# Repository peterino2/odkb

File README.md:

# ODKB - Collection repository for the stm32 based keyboard project

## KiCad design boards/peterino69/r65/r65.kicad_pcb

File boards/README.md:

# Boards

This is a submodul of the odkb\_top repositoy.

These files were intially created in kicad 4 but will be migrated to kicad five

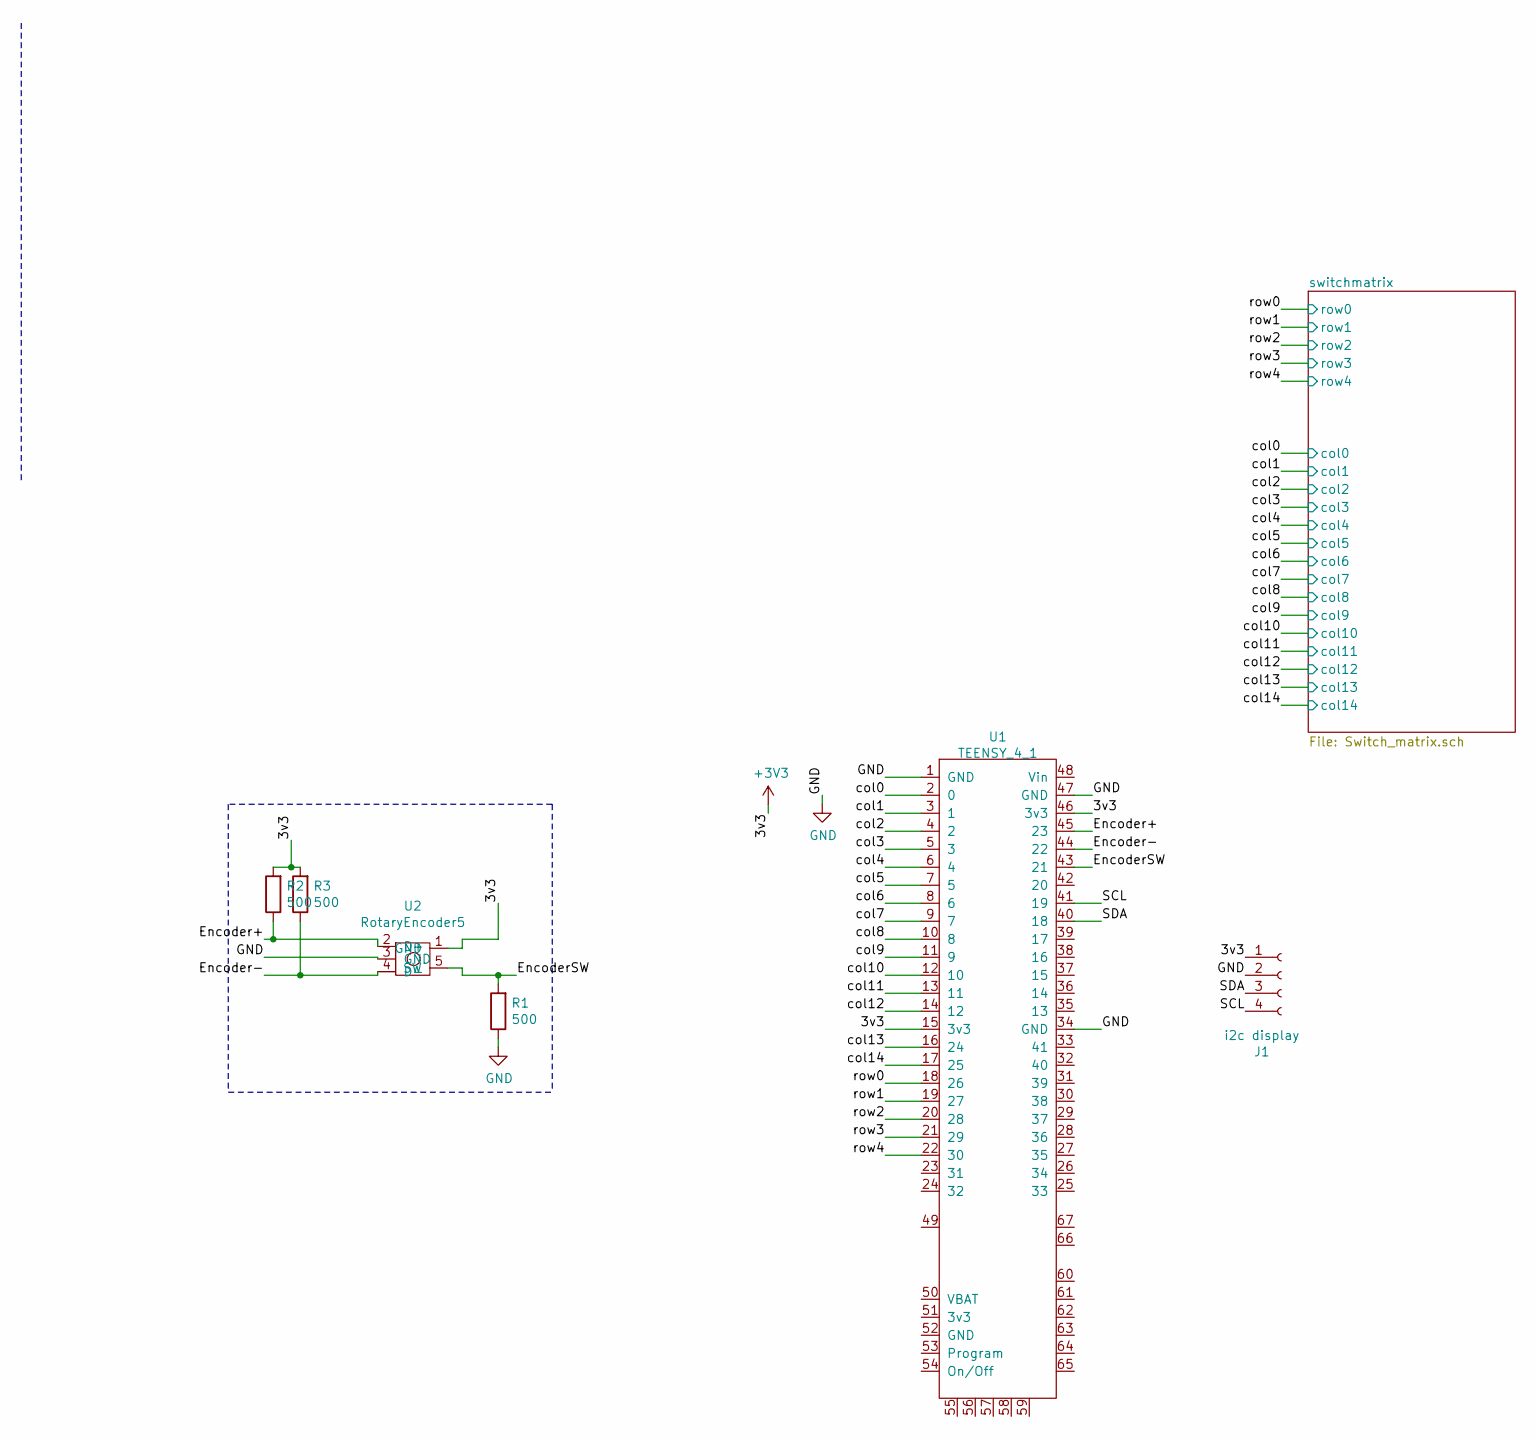
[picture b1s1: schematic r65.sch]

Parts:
J1: i2c display; LCD_DISPLAY
R1, R2, R3: 500; R_Axial_DIN0207_L6.3mm_D2.5mm_P15.24mm_Horizontal
U1: TEENSY_4_1; Teensy41_no_inners
U2: RotaryEncoder5; SF-ROTARY-ENCODER

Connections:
+3V3: J1.1, R2.2, R3.2, U1.15 (3v3), U1.46 (3v3), U2.1 (GND)
/Encoder+: R2.1, U1.45 (23), U2.2 (D+)
/Encoder-: R3.1, U1.44 (22), U2.4 (D-)
/EncoderSW: R1.2, U1.43 (21), U2.5 (SW)
/SCL: J1.4, U1.41 (19)
/SDA: J1.3, U1.40 (18)
/col0: U1.2 (0); also elsewhere on the board
/col1: U1.3 (1); also elsewhere on the board
/col2: U1.4 (2); also elsewhere on the board
/col3: U1.5 (3); also elsewhere on the board
/col4: U1.6 (4); also elsewhere on the board
/col5: U1.7 (5); also elsewhere on the board
/col6: U1.8 (6); also elsewhere on the board
/col7: U1.9 (7); also elsewhere on the board
/col8: U1.10 (8); also elsewhere on the board
/col9: U1.11 (9); also elsewhere on the board
/col10: U1.12 (10); also elsewhere on the board
/col11: U1.13 (11); also elsewhere on the board
/col12: U1.14 (12); also elsewhere on the board
/col13: U1.16 (24); also elsewhere on the board
/col14: U1.17 (25); also elsewhere on the board
/row0: U1.18 (26); also elsewhere on the board
/row1: U1.19 (27); also elsewhere on the board
/row2: U1.20 (28); also elsewhere on the board
/row3: U1.21 (29); also elsewhere on the board
/row4: U1.22 (30); also elsewhere on the board
GND: J1.2, R1.1, U1.1 (GND), U1.34 (GND), U1.47 (GND), U2.3 (GND)

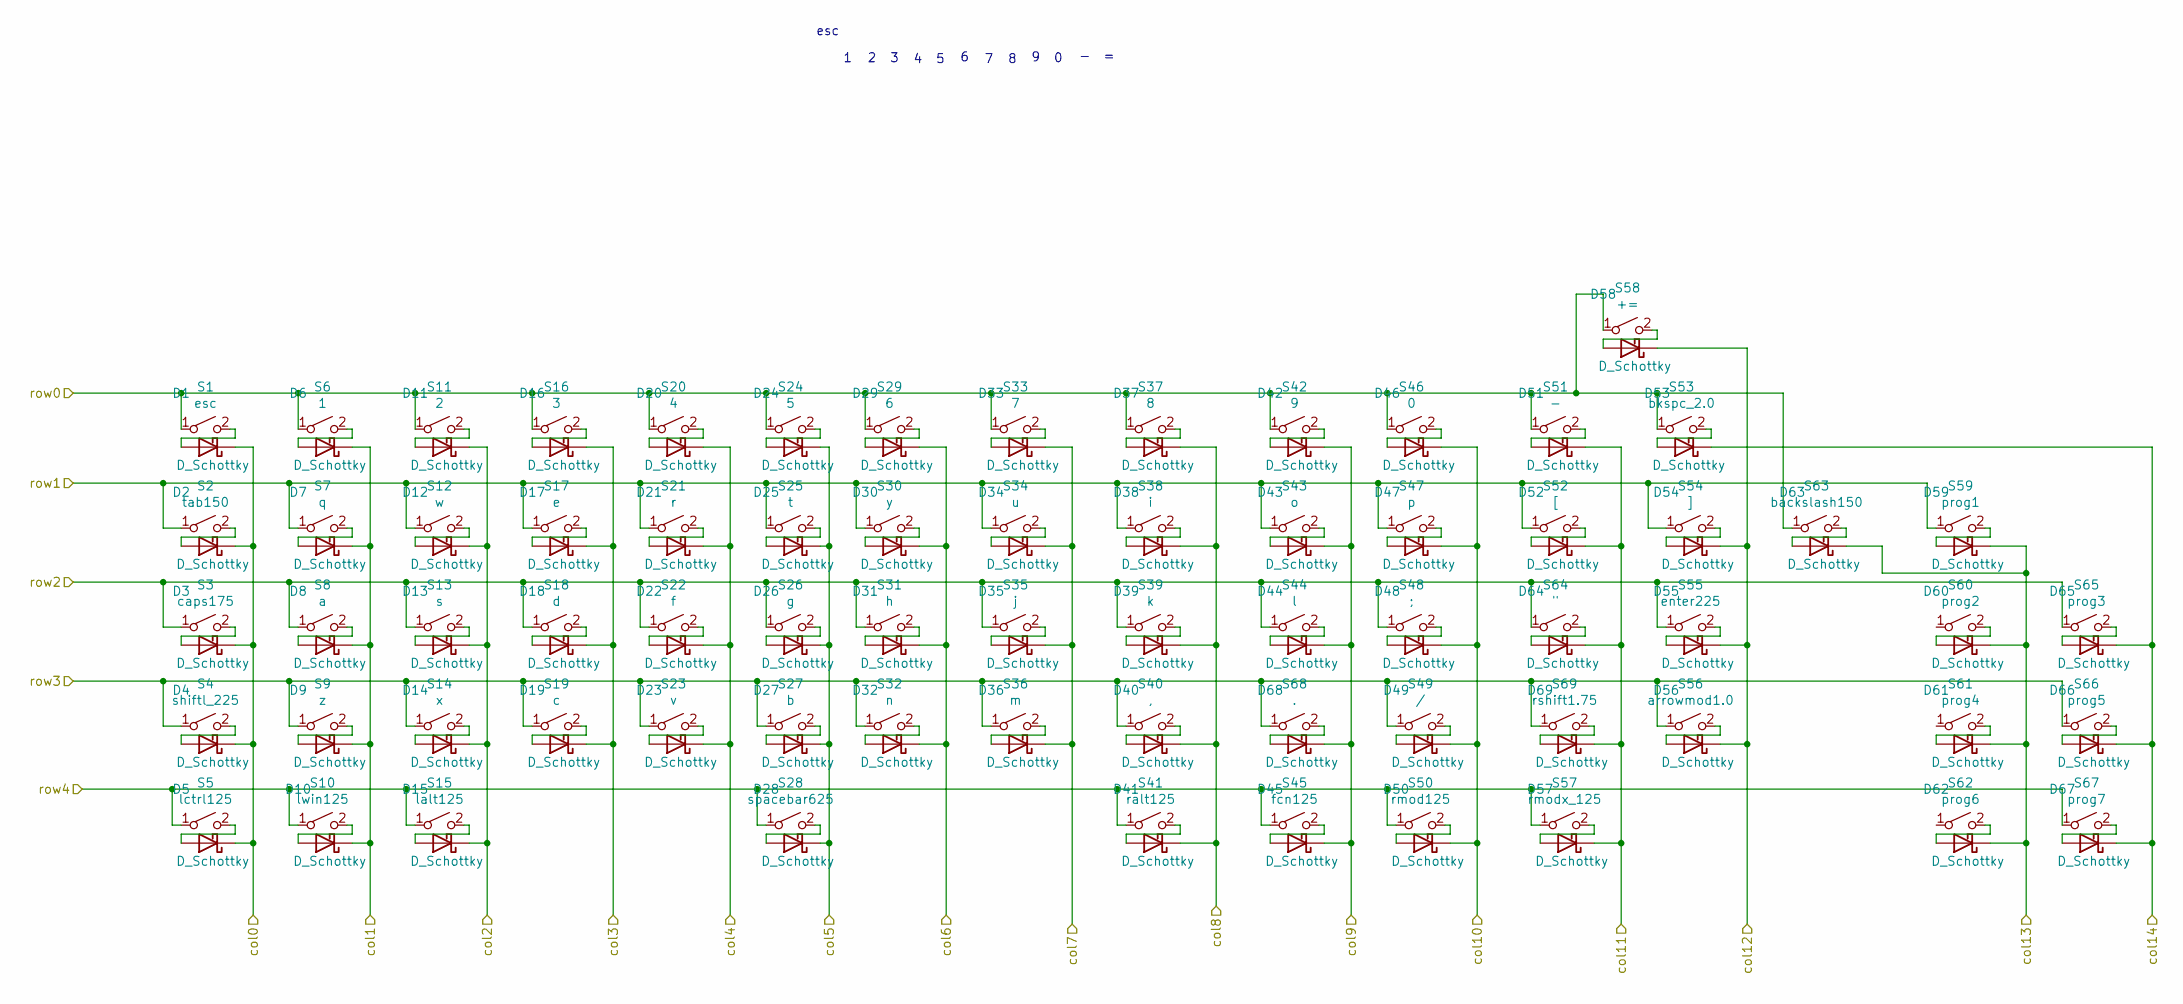
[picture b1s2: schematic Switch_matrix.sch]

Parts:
D1, D2, D3, D4, D5, D6, D7, D8, D9, D10, D11, D12, D13, D14, D15, D16, D17, D18, D19, D20, D21, D22, D23, D24, D25, D26, D27, D28, D29, D30, D31, D32, D33, D34, D35, D36, D37, D38, D39, D40, D41, D42, D43, D44, D45, D46, D47, D48, D49, D50, D51, D52, D53, D54, D55, D56, D57, D58, D59, D60, D61, D62, D63, D64, D65, D66, D67, D68, D69: D_Schottky; D_DO-41_SOD81_P10.16mm_Horizontal
S1: esc; SW_Cherry_MX_1.00u_Plate
S2: tab150; SW_Cherry_MX_1.50u_PCB
S3: caps175; SW_Cherry_MX_1.75u_PCB
S4: shiftl_225; SW_Cherry_MX_2.25u_PCB
S5: lctrl125; SW_Cherry_MX_1.25u_PCB
S6: 1; SW_Cherry_MX_1.00u_Plate
S7: q; SW_Cherry_MX_1.00u_Plate
S8: a; SW_Cherry_MX_1.00u_Plate
S9: z; SW_Cherry_MX_1.00u_Plate
S10: lwin125; SW_Cherry_MX_1.25u_PCB
S11: 2; SW_Cherry_MX_1.00u_Plate
S12: w; SW_Cherry_MX_1.00u_Plate
S13: s; SW_Cherry_MX_1.00u_Plate
S14: x; SW_Cherry_MX_1.00u_Plate
S15: lalt125; SW_Cherry_MX_1.25u_PCB
S16: 3; SW_Cherry_MX_1.00u_Plate
S17: e; SW_Cherry_MX_1.00u_Plate
S18: d; SW_Cherry_MX_1.00u_Plate
S19: c; SW_Cherry_MX_1.00u_Plate
S20: 4; SW_Cherry_MX_1.00u_Plate
S21: r; SW_Cherry_MX_1.00u_Plate
S22: f; SW_Cherry_MX_1.00u_Plate
S23: v; SW_Cherry_MX_1.00u_Plate
S24: 5; SW_Cherry_MX_1.00u_Plate
S25: t; SW_Cherry_MX_1.00u_Plate
S26: g; SW_Cherry_MX_1.00u_Plate
S27: b; SW_Cherry_MX_1.00u_Plate
S28: spacebar625; SW_Cherry_MX_6.25u_PCB
S29: 6; SW_Cherry_MX_1.00u_Plate
S30: y; SW_Cherry_MX_1.00u_Plate
S31: h; SW_Cherry_MX_1.00u_Plate
S32: n; SW_Cherry_MX_1.00u_Plate
S33: 7; SW_Cherry_MX_1.00u_Plate
S34: u; SW_Cherry_MX_1.00u_Plate
S35: j; SW_Cherry_MX_1.00u_Plate
S36: m; SW_Cherry_MX_1.00u_Plate
S37: 8; SW_Cherry_MX_1.00u_Plate
S38: i; SW_Cherry_MX_1.00u_Plate
S39: k; SW_Cherry_MX_1.00u_Plate
S40: ,; SW_Cherry_MX_1.00u_Plate
S41: ralt125; SW_Cherry_MX_1.25u_PCB
S42: 9; SW_Cherry_MX_1.00u_Plate
S43: o; SW_Cherry_MX_1.00u_Plate
S44: l; SW_Cherry_MX_1.00u_Plate
S45: fcn125; SW_Cherry_MX_1.25u_PCB
S46: 0; SW_Cherry_MX_1.00u_Plate
S47: p; SW_Cherry_MX_1.00u_Plate
S48: ;; SW_Cherry_MX_1.00u_Plate
S49: /; SW_Cherry_MX_1.00u_Plate
S50: rmod125; SW_Cherry_MX_1.25u_PCB
S51: -; SW_Cherry_MX_1.00u_Plate
S52: [; SW_Cherry_MX_1.00u_Plate
S53: bkspc_2.0; SW_Cherry_MX_2.00u_PCB
S54: ]; SW_Cherry_MX_1.00u_Plate
S55: enter225; SW_Cherry_MX_2.25u_PCB
S56: arrowmod1.0; SW_Cherry_MX_1.00u_Plate
S57: rmodx_125; SW_Cherry_MX_1.25u_PCB
S58: +=; SW_Cherry_MX_1.00u_Plate
S59: prog1; SW_Cherry_MX_1.00u_Plate
S60: prog2; SW_Cherry_MX_1.00u_Plate
S61: prog4; SW_Cherry_MX_1.00u_Plate
S62: prog6; SW_Cherry_MX_1.00u_Plate
S63: backslash150; SW_Cherry_MX_1.50u_PCB
S64: \"; SW_Cherry_MX_1.00u_Plate
S65: prog3; SW_Cherry_MX_1.00u_Plate
S66: prog5; SW_Cherry_MX_1.00u_Plate
S67: prog7; SW_Cherry_MX_1.00u_Plate
S68: .; SW_Cherry_MX_1.00u_Plate
S69: rshift1.75; SW_Cherry_MX_1.75u_PCB

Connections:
/col0: D1.1 (K), D2.1 (K), D3.1 (K), D4.1 (K), D5.1 (K); also elsewhere on the board
/col1: D6.1 (K), D7.1 (K), D8.1 (K), D9.1 (K), D10.1 (K); also elsewhere on the board
/col2: D11.1 (K), D12.1 (K), D13.1 (K), D14.1 (K), D15.1 (K); also elsewhere on the board
/col3: D16.1 (K), D17.1 (K), D18.1 (K), D19.1 (K); also elsewhere on the board
/col4: D20.1 (K), D21.1 (K), D22.1 (K), D23.1 (K); also elsewhere on the board
/col5: D24.1 (K), D25.1 (K), D26.1 (K), D27.1 (K), D28.1 (K); also elsewhere on the board
/col6: D29.1 (K), D30.1 (K), D31.1 (K), D32.1 (K); also elsewhere on the board
/col7: D33.1 (K), D34.1 (K), D35.1 (K), D36.1 (K); also elsewhere on the board
/col8: D37.1 (K), D38.1 (K), D39.1 (K), D40.1 (K), D41.1 (K); also elsewhere on the board
/col9: D42.1 (K), D43.1 (K), D44.1 (K), D45.1 (K), D68.1 (K); also elsewhere on the board
/col10: D46.1 (K), D47.1 (K), D48.1 (K), D49.1 (K), D50.1 (K); also elsewhere on the board
/col11: D51.1 (K), D52.1 (K), D57.1 (K), D64.1 (K), D69.1 (K); also elsewhere on the board
/col12: D54.1 (K), D55.1 (K), D56.1 (K), D58.1 (K); also elsewhere on the board
/col13: D59.1 (K), D60.1 (K), D61.1 (K), D62.1 (K), D63.1 (K); also elsewhere on the board
/col14: D53.1 (K), D65.1 (K), D66.1 (K), D67.1 (K); also elsewhere on the board
/row0: S1.1, S6.1, S11.1, S16.1, S20.1, S24.1, S29.1, S33.1, S37.1, S42.1, S46.1, S51.1, S53.1, S58.1, S63.1; also elsewhere on the board
/row1: S2.1, S7.1, S12.1, S17.1, S21.1, S25.1, S30.1, S34.1, S38.1, S43.1, S47.1, S52.1, S54.1, S59.1; also elsewhere on the board
/row2: S3.1, S8.1, S13.1, S18.1, S22.1, S26.1, S31.1, S35.1, S39.1, S44.1, S48.1, S55.1, S64.1, S65.1; also elsewhere on the board
/row3: S4.1, S9.1, S14.1, S19.1, S23.1, S27.1, S32.1, S36.1, S40.1, S49.1, S56.1, S66.1, S68.1, S69.1; also elsewhere on the board
/row4: S5.1, S10.1, S15.1, S28.1, S41.1, S45.1, S50.1, S57.1, S67.1; also elsewhere on the board
unnamed: D1.2 (A), S1.2
unnamed: D2.2 (A), S2.2
unnamed: D3.2 (A), S3.2
unnamed: D4.2 (A), S4.2
unnamed: D5.2 (A), S5.2
unnamed: D6.2 (A), S6.2
unnamed: D7.2 (A), S7.2
unnamed: D8.2 (A), S8.2
unnamed: D9.2 (A), S9.2
unnamed: D10.2 (A), S10.2
unnamed: D11.2 (A), S11.2
unnamed: D12.2 (A), S12.2
unnamed: D13.2 (A), S13.2
unnamed: D14.2 (A), S14.2
unnamed: D15.2 (A), S15.2
unnamed: D16.2 (A), S16.2
unnamed: D17.2 (A), S17.2
unnamed: D18.2 (A), S18.2
unnamed: D19.2 (A), S19.2
unnamed: D20.2 (A), S20.2
unnamed: D21.2 (A), S21.2
unnamed: D22.2 (A), S22.2
unnamed: D23.2 (A), S23.2
unnamed: D24.2 (A), S24.2
unnamed: D25.2 (A), S25.2
unnamed: D26.2 (A), S26.2
unnamed: D27.2 (A), S27.2
unnamed: D28.2 (A), S28.2
unnamed: D29.2 (A), S29.2
unnamed: D30.2 (A), S30.2
unnamed: D31.2 (A), S31.2
unnamed: D32.2 (A), S32.2
unnamed: D33.2 (A), S33.2
unnamed: D34.2 (A), S34.2
unnamed: D35.2 (A), S35.2
unnamed: D36.2 (A), S36.2
unnamed: D37.2 (A), S37.2
unnamed: D38.2 (A), S38.2
unnamed: D39.2 (A), S39.2
unnamed: D40.2 (A), S40.2
unnamed: D41.2 (A), S41.2
unnamed: D42.2 (A), S42.2
unnamed: D43.2 (A), S43.2
unnamed: D44.2 (A), S44.2
unnamed: D45.2 (A), S45.2
unnamed: D46.2 (A), S46.2
unnamed: D47.2 (A), S47.2
unnamed: D48.2 (A), S48.2
unnamed: D49.2 (A), S49.2
unnamed: D50.2 (A), S50.2
unnamed: D51.2 (A), S51.2
unnamed: D52.2 (A), S52.2
unnamed: D53.2 (A), S53.2
unnamed: D54.2 (A), S54.2
unnamed: D55.2 (A), S55.2
unnamed: D56.2 (A), S56.2
unnamed: D57.2 (A), S57.2
unnamed: D58.2 (A), S58.2
unnamed: D59.2 (A), S59.2
unnamed: D60.2 (A), S60.2
unnamed: D61.2 (A), S61.2
unnamed: D62.2 (A), S62.2
unnamed: D63.2 (A), S63.2
unnamed: D64.2 (A), S64.2
unnamed: D65.2 (A), S65.2
unnamed: D66.2 (A), S66.2
unnamed: D67.2 (A), S67.2
unnamed: D68.2 (A), S68.2
unnamed: D69.2 (A), S69.2

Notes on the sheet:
esc

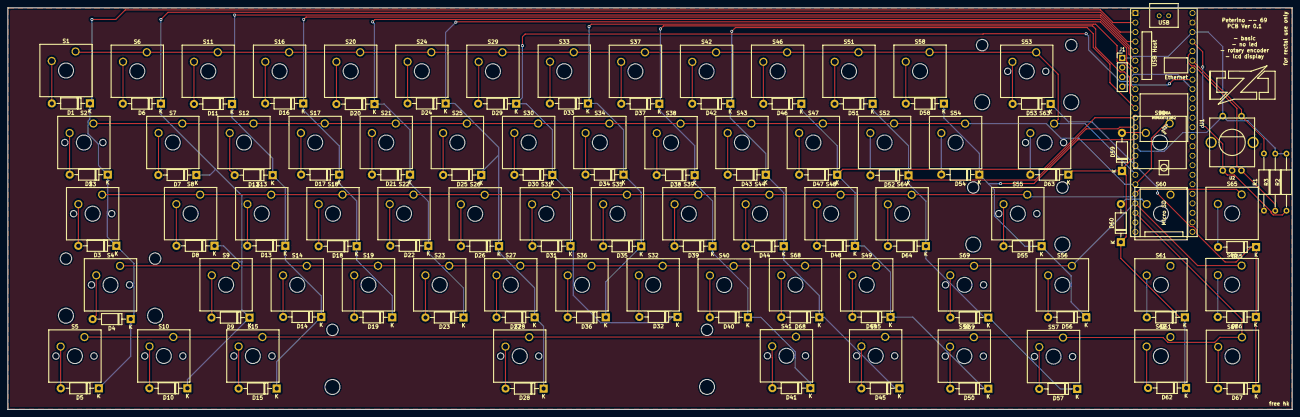
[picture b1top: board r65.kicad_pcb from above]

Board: 2 copper layers, 342.9 x 107.2 mm, 144 parts (0 on the bottom side), 96 nets.

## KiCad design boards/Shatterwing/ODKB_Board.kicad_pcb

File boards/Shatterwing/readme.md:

# Shatterwing -- 4th generation keyboard.

Key features:
* Split design
* USB-C
* LEDs with control (non-rgb because rgb is for losers)

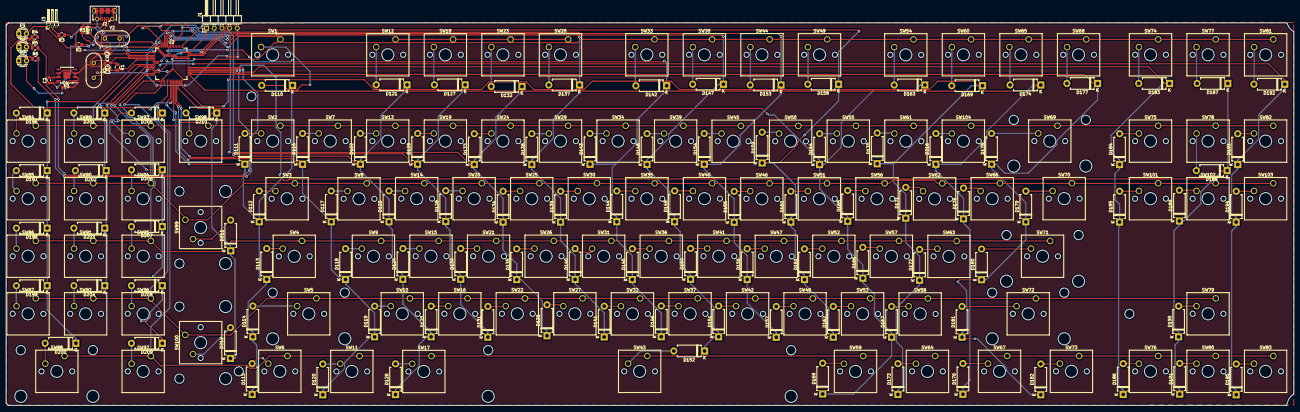
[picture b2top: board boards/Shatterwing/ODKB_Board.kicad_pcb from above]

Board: 2 copper layers, 425.0 x 131.8 mm, 232 parts (0 on the bottom side), 153 nets.

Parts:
C1: 0.1uF; C_0603_1608Metric_Pad1.05x0.95mm_HandSolder
C2, C3, C5, C6: 20pf; C_0603_1608Metric_Pad1.05x0.95mm_HandSolder
C4: 2.2uF; C_0603_1608Metric_Pad1.05x0.95mm_HandSolder
D1: led_caps; LED_D3.0mm_Clear
D2: led_scrlk; LED_D3.0mm_Clear
D3: led_numlk; LED_D3.0mm_Clear
D110, D111, D112, D113, D114, D115, D116, D117, D118, D119, D120, D121, D122, D123, D124, D125, D126, D127, D128, D129, D130, D131, D132, D133, D134, D135, D136, D137, D138, D139, D140, D141, D142, D143, D144, D145, D146, D147, D148, D149, D150, D151, D152, D153, D154, D155, D156, D157, D158, D159, D160, D161, D162, D163, D164, D165, D166, D167, D168, D169, D170, D171, D172, D173, D174, D175, D176, D177, D178, D179, D180, D181, D182, D183, D184, D185, D186, D187, D188, D189, D190, D191, D192, D193, D194, D195, D196, D197, D198, D199, D200, D201, D202, D203, D204, D205, D206, D207, D208, D209, D210, D211, D212, D216: D_Schottky; D_DO-15_P10.16mm_Horizontal
J1: Conn_01x05_Male; PinHeader_1x05_P2.54mm_Horizontal
J2: USB_B_Micro; USB_Micro-B_Molex-105017-0001
J3: Conn_01x03_Male; PinHeader_1x03_P1.27mm_Horizontal
R1: 1M; R_0805_2012Metric
R2: 1.5k; R_0805_2012Metric
R3: 10k; R_0805_2012Metric
R4, R5, R6: R; R_0805_2012Metric
R10, R11: 20; R_0805_2012Metric
SW1: ESC; SW_Cherry_MX1A_1.00u_PCB
SW2: `; SW_Cherry_MX1A_1.00u_PCB
SW3: TAB; SW_Cherry_MX1A_1.50u_PCB
SW4: CAPS; SW_Cherry_MX1A_1.75u_PCB
SW5: LSHIFT; SW_Cherry_MX1A_2.25u_PCB
SW6, SW73: CTRL; SW_Cherry_MX1A_1.25u_PCB
SW7, SW87: 1; SW_Cherry_MX1A_1.00u_PCB
SW8: Q; SW_Cherry_MX1A_1.00u_PCB
SW9: A; SW_Cherry_MX1A_1.00u_PCB
SW10: Z; SW_Cherry_MX1A_1.00u_PCB
SW11: WIN; SW_Cherry_MX1A_1.25u_PCB
SW12: F1; SW_Cherry_MX1A_1.00u_PCB
SW13, SW92: 2; SW_Cherry_MX1A_1.00u_PCB
SW14: W; SW_Cherry_MX1A_1.00u_PCB
SW15: S; SW_Cherry_MX1A_1.00u_PCB
SW16: X; SW_Cherry_MX1A_1.00u_PCB
SW17, SW59: ALT; SW_Cherry_MX1A_1.25u_PCB
SW18: F2; SW_Cherry_MX1A_1.00u_PCB
SW19, SW96: 3; SW_Cherry_MX1A_1.00u_PCB
SW20: E; SW_Cherry_MX1A_1.00u_PCB
SW21: D; SW_Cherry_MX1A_1.00u_PCB
SW22: C; SW_Cherry_MX1A_1.00u_PCB
SW23: F3; SW_Cherry_MX1A_1.00u_PCB
SW24, SW86: 4; SW_Cherry_MX1A_1.00u_PCB
SW25: R; SW_Cherry_MX1A_1.00u_PCB
SW26: F; SW_Cherry_MX1A_1.00u_PCB
SW27: V; SW_Cherry_MX1A_1.00u_PCB
SW28: F4; SW_Cherry_MX1A_1.00u_PCB
SW29, SW91: 5; SW_Cherry_MX1A_1.00u_PCB
SW30: T; SW_Cherry_MX1A_1.00u_PCB
SW31: G; SW_Cherry_MX1A_1.00u_PCB
SW32: B; SW_Cherry_MX1A_1.00u_PCB
SW33: F5; SW_Cherry_MX1A_1.00u_PCB
SW34, SW95: 6; SW_Cherry_MX1A_1.00u_PCB
SW35: Y; SW_Cherry_MX1A_1.00u_PCB
SW36: H; SW_Cherry_MX1A_1.00u_PCB
SW37: N; SW_Cherry_MX1A_1.00u_PCB
SW38: F6; SW_Cherry_MX1A_1.00u_PCB
SW39, SW85: 7; SW_Cherry_MX1A_1.00u_PCB
SW40: U; SW_Cherry_MX1A_1.00u_PCB
SW41: J; SW_Cherry_MX1A_1.00u_PCB
SW42: M; SW_Cherry_MX1A_1.00u_PCB
SW43: SPC; SW_Cherry_MX1A_6.25u_PCB
SW44: F7; SW_Cherry_MX1A_1.00u_PCB
SW45, SW90: 8; SW_Cherry_MX1A_1.00u_PCB
SW46: I; SW_Cherry_MX1A_1.00u_PCB
SW47: K; SW_Cherry_MX1A_1.00u_PCB
SW48: ,<; SW_Cherry_MX1A_1.00u_PCB
SW49: F8; SW_Cherry_MX1A_1.00u_PCB
SW50, SW94: 9; SW_Cherry_MX1A_1.00u_PCB
SW51: O; SW_Cherry_MX1A_1.00u_PCB
SW52: L; SW_Cherry_MX1A_1.00u_PCB
SW53: .>; SW_Cherry_MX1A_1.00u_PCB
SW54: F9; SW_Cherry_MX1A_1.00u_PCB
SW55: 0; SW_Cherry_MX1A_1.00u_PCB
SW56: P; SW_Cherry_MX1A_1.00u_PCB
SW57: ;; SW_Cherry_MX1A_1.00u_PCB
SW58: /?; SW_Cherry_MX1A_1.00u_PCB
SW60: F10; SW_Cherry_MX1A_1.00u_PCB
SW61, SW98: -; SW_Cherry_MX1A_1.00u_PCB
SW62: [; SW_Cherry_MX1A_1.00u_PCB
SW63: '; SW_Cherry_MX1A_1.00u_PCB
SW64: FN; SW_Cherry_MX1A_1.25u_PCB
SW65: F11; SW_Cherry_MX1A_1.00u_PCB
SW66: ]; SW_Cherry_MX1A_1.00u_PCB
SW67: FXN; SW_Cherry_MX1A_1.25u_PCB
SW68: F12; SW_Cherry_MX1A_1.00u_PCB
SW69: BACKSPACE; SW_Cherry_MX1A_2.00u_PCB
SW70: \; SW_Cherry_MX1A_1.00u_PCB
SW71: ENTER; SW_Cherry_MX1A_2.25u_PCB
SW72: RSHIFT; SW_Cherry_MX1A_2.75u_PCB
SW74: PRINT; SW_Cherry_MX1A_1.00u_PCB
SW75: INS; SW_Cherry_MX1A_1.00u_PCB
SW76: ARROW_LEFT; SW_Cherry_MX1A_1.00u_PCB
SW77: SCRLK; SW_Cherry_MX1A_1.00u_PCB
SW78: HOME; SW_Cherry_MX1A_1.00u_PCB
SW79: ARROW_UP; SW_Cherry_MX1A_1.00u_PCB
SW80: ARROW_DOWN; SW_Cherry_MX1A_1.00u_PCB
SW81: PAUSE; SW_Cherry_MX1A_1.00u_PCB
SW82: PAGEUP; SW_Cherry_MX1A_1.00u_PCB
SW83: ARROW_RIGHT; SW_Cherry_MX1A_1.00u_PCB
SW84: NUMLK; SW_Cherry_MX1A_1.00u_PCB
SW88: 0; SW_Cherry_MX1A_2.00u_PCB
SW89: /; SW_Cherry_MX1A_1.00u_PCB
SW93: *; SW_Cherry_MX1A_1.00u_PCB
SW97: .; SW_Cherry_MX1A_1.00u_PCB
SW99: +; SW_Cherry_MX1A_2.00u_PCB
SW100: ENT; SW_Cherry_MX1A_2.00u_PCB
SW101: DEL; SW_Cherry_MX1A_1.00u_PCB
SW102: END; SW_Cherry_MX1A_1.00u_PCB
SW103: PGDN; SW_Cherry_MX1A_1.00u_PCB
SW104: =; SW_Cherry_MX1A_1.00u_PCB
U1: L4931ABD33-TR; SOIC-8-1EP_3.9x4.9mm_P1.27mm_EP2.35x2.35mm
U2: STM32F103RCTx; LQFP-64_10x10mm_P0.5mm
Y1: 8MHz; Crystal_HC49-4H_Vertical
Y2: 32.786k; Crystal_HC49-4H_Vertical

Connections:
+3V3: C4.1, D1.2, D2.2, D3.2, J1.1, J3.1, U1.1, U2.1, U2.13, U2.19, U2.32, U2.48, U2.64
+5V: C1.1, J2.1, R2.1, U1.8
/LED_CAPS: R4.2, U2.25
/LED_NUMLK: R6.2, U2.38
/LED_SCRLK: R5.2, U2.37
/LSE_OSC_IN: C5.1, U2.3, Y2.1
/LSE_OSC_OUT: C6.1, U2.4, Y2.2
/NRST: J1.2, U2.7
/OSC_IN: C2.1, R1.1, U2.5, Y1.1
/OSC_OUT: C3.1, R1.2, U2.6, Y1.2
/SWDCLK: J1.3, U2.49
/SWDIO: J1.4, U2.46
/USB_DM: R11.1, U2.44
/USB_DP: R10.2, U2.45
/col0: D110.1, D111.1, D112.1, D113.1, D114.1, D115.1, U2.26
/col1: D116.1, D117.1, D118.1, D119.1, D120.1, U2.27
/col2: D121.1, D122.1, D123.1, D124.1, D125.1, D126.1, U2.28
/col3: D127.1, D128.1, D129.1, D130.1, D131.1, U2.55
/col4: D132.1, D133.1, D134.1, D135.1, D136.1, U2.56
/col5: D137.1, D138.1, D139.1, D140.1, D141.1, U2.57
/col6: D142.1, D143.1, D144.1, D145.1, D146.1, U2.58
/col7: D147.1, D148.1, D149.1, D150.1, D151.1, D152.1, U2.59
/col8: D153.1, D154.1, D155.1, D156.1, D157.1, U2.61
/col9: D158.1, D159.1, D160.1, D161.1, D162.1, U2.62
/col10: D163.1, D164.1, D165.1, D166.1, D167.1, D168.1, U2.29
/col11: D169.1, D170.1, D171.1, D172.1, D173.1, U2.30
/col12: D174.1, D175.1, D176.1, D216.1, U2.33
/col13: D177.1, D178.1, D179.1, D180.1, D181.1, D182.1, U2.34
/col14: D183.1, D184.1, D185.1, D186.1, U2.35
/col15: D187.1, D188.1, D189.1, D190.1, D191.1, U2.36
/col16: D192.1, D193.1, D194.1, D195.1, U2.8
/col17: D196.1, D197.1, D198.1, D199.1, D200.1, U2.9
/col18: D201.1, D202.1, D203.1, D204.1, U2.10
/col19: D205.1, D206.1, D207.1, D208.1, D209.1, U2.11
/col20: D210.1, D211.1, D212.1, U2.24
/row0: SW1.1, SW12.1, SW18.1, SW23.1, SW28.1, SW33.1, SW38.1, SW44.1, SW49.1, SW54.1, SW60.1, SW65.1, SW68.1, SW74.1, SW77.1, SW81.1, U2.14
/row1: SW2.1, SW7.1, SW13.1, SW19.1, SW24.1, SW29.1, SW34.1, SW39.1, SW45.1, SW50.1, SW55.1, SW61.1, SW69.1, SW75.1, SW78.1, SW82.1, SW84.1, SW89.1, SW93.1, SW98.1, SW104.1, U2.15
/row2: SW3.1, SW8.1, SW14.1, SW20.1, SW25.1, SW30.1, SW35.1, SW40.1, SW46.1, SW51.1, SW56.1, SW62.1, SW66.1, SW70.1, SW85.1, SW90.1, SW94.1, SW99.1, SW101.1, SW102.1, SW103.1, U2.16
/row3: SW4.1, SW9.1, SW15.1, SW21.1, SW26.1, SW31.1, SW36.1, SW41.1, SW47.1, SW52.1, SW57.1, SW63.1, SW71.1, SW86.1, SW91.1, SW95.1, U2.17
/row4: SW5.1, SW10.1, SW16.1, SW22.1, SW27.1, SW32.1, SW37.1, SW42.1, SW48.1, SW53.1, SW58.1, SW72.1, SW79.1, SW87.1, SW92.1, SW96.1, SW100.1, U2.20
/row5: SW6.1, SW11.1, SW17.1, SW43.1, SW59.1, SW64.1, SW67.1, SW73.1, SW76.1, SW80.1, SW83.1, SW88.1, SW97.1, U2.22
GND: C1.2, C2.2, C3.2, C4.2, C5.2, C6.2, J1.5, J2.5, J2.6, J3.3, U1.2, U1.3, U1.6, U1.7, U2.12, U2.18, U2.31, U2.47, U2.63
unnamed: D1.1, R4.1
unnamed: D2.1, R5.1
unnamed: D3.1, R6.1
unnamed: D110.2, SW1.2
unnamed: D111.2, SW2.2
unnamed: D112.2, SW3.2
unnamed: D113.2, SW4.2
unnamed: D114.2, SW5.2
unnamed: D115.2, SW6.2
unnamed: D116.2, SW7.2
unnamed: D117.2, SW8.2
unnamed: D118.2, SW9.2
unnamed: D119.2, SW10.2
unnamed: D120.2, SW11.2
unnamed: D121.2, SW12.2
unnamed: D122.2, SW13.2
unnamed: D123.2, SW14.2
unnamed: D124.2, SW15.2
unnamed: D125.2, SW16.2
unnamed: D126.2, SW17.2
unnamed: D127.2, SW18.2
unnamed: D128.2, SW19.2
unnamed: D129.2, SW20.2
unnamed: D130.2, SW21.2
unnamed: D131.2, SW22.2
unnamed: D132.2, SW23.2
unnamed: D133.2, SW24.2
unnamed: D134.2, SW25.2
unnamed: D135.2, SW26.2
unnamed: D136.2, SW27.2
unnamed: D137.2, SW28.2
unnamed: D138.2, SW29.2
unnamed: D139.2, SW30.2
unnamed: D140.2, SW31.2
unnamed: D141.2, SW32.2
unnamed: D142.2, SW33.2
unnamed: D143.2, SW34.2
unnamed: D144.2, SW35.2
unnamed: D145.2, SW36.2
unnamed: D146.2, SW37.2
unnamed: D147.2, SW38.2
unnamed: D148.2, SW39.2
unnamed: D149.2, SW40.2
unnamed: D150.2, SW41.2
unnamed: D151.2, SW42.2
unnamed: D152.2, SW43.2
unnamed: D153.2, SW44.2
unnamed: D154.2, SW45.2
unnamed: D155.2, SW46.2
unnamed: D156.2, SW47.2
unnamed: D157.2, SW48.2
unnamed: D158.2, SW49.2
unnamed: D159.2, SW50.2
unnamed: D160.2, SW51.2
unnamed: D161.2, SW52.2
unnamed: D162.2, SW53.2
unnamed: D163.2, SW54.2
unnamed: D164.2, SW55.2
unnamed: D165.2, SW56.2
unnamed: D166.2, SW57.2
unnamed: D167.2, SW58.2
unnamed: D168.2, SW59.2
unnamed: D169.2, SW60.2
unnamed: D170.2, SW61.2
unnamed: D171.2, SW62.2
unnamed: D172.2, SW63.2
unnamed: D173.2, SW64.2
unnamed: D174.2, SW65.2
unnamed: D175.2, SW66.2
unnamed: D176.2, SW67.2
unnamed: D177.2, SW68.2
unnamed: D178.2, SW69.2
unnamed: D179.2, SW70.2
unnamed: D180.2, SW71.2
unnamed: D181.2, SW72.2
unnamed: D182.2, SW73.2
unnamed: D183.2, SW74.2
unnamed: D184.2, SW75.2
unnamed: D185.2, SW101.2
unnamed: D186.2, SW76.2
unnamed: D187.2, SW77.2
unnamed: D188.2, SW78.2
unnamed: D189.2, SW102.2
unnamed: D190.2, SW79.2
unnamed: D191.2, SW80.2
unnamed: D192.2, SW81.2
unnamed: D193.2, SW82.2
unnamed: D194.2, SW103.2
unnamed: D195.2, SW83.2
unnamed: D196.2, SW84.2
unnamed: D197.2, SW85.2
unnamed: D198.2, SW86.2
unnamed: D199.2, SW87.2
unnamed: D200.2, SW88.2
unnamed: D201.2, SW89.2
unnamed: D202.2, SW90.2
unnamed: D203.2, SW91.2
unnamed: D204.2, SW92.2
unnamed: D205.2, SW93.2
unnamed: D206.2, SW94.2
unnamed: D207.2, SW95.2
unnamed: D208.2, SW96.2
unnamed: D209.2, SW97.2
unnamed: D210.2, SW98.2
unnamed: D211.2, SW99.2
unnamed: D212.2, SW100.2
unnamed: D216.2, SW104.2
unnamed: J2.2, R11.2
unnamed: J2.3, R2.2, R10.1
unnamed: J3.2, R3.2
unnamed: R3.1, U2.60

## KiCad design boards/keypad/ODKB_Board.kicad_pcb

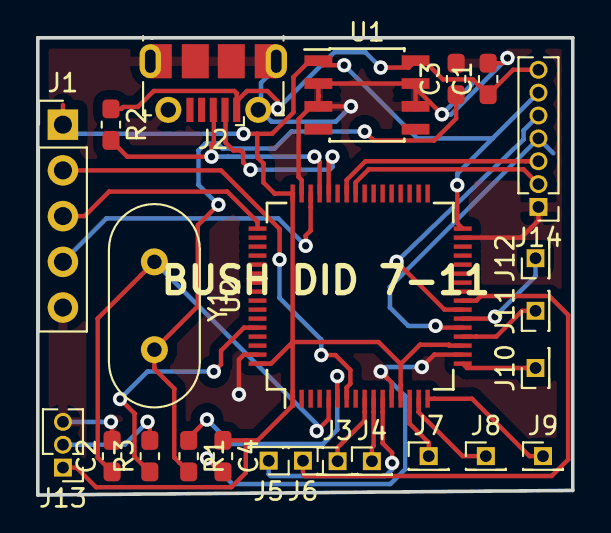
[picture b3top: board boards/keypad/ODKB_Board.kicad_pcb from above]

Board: 2 copper layers, 29.7 x 25.4 mm, 24 parts (0 on the bottom side), 27 nets.

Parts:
C1: 0.1uF; C_0603_1608Metric_Pad1.05x0.95mm_HandSolder
C2, C3: 16pf; C_0603_1608Metric_Pad1.05x0.95mm_HandSolder
C4: 2.2uF; C_0603_1608Metric_Pad1.05x0.95mm_HandSolder
J1: jtag; PinHeader_1x05_P2.54mm_Vertical
J2: USB_B_Micro; USB_Micro-B_Molex-105017-0001
J3: Col17; PinHeader_1x01_P1.27mm_Vertical
J4: col18; PinHeader_1x01_P1.27mm_Vertical
J5: col19; PinHeader_1x01_P1.27mm_Vertical
J6: col20; PinHeader_1x01_P1.27mm_Vertical
J7: row0; PinHeader_1x01_P1.27mm_Vertical
J8: row1; PinHeader_1x01_P1.27mm_Vertical
J9: row2; PinHeader_1x01_P1.27mm_Vertical
J10: row3; PinHeader_1x01_P1.27mm_Vertical
J11: row4; PinHeader_1x01_P1.27mm_Vertical
J12: row5; PinHeader_1x01_P1.27mm_Vertical
J13: Bootpin; PinHeader_1x03_P1.27mm_Vertical
J14: spi; PinHeader_1x07_P1.27mm_Vertical
R1: 1.3k; R_0603_1608Metric_Pad1.05x0.95mm_HandSolder
R2: 1.5k; R_0603_1608Metric_Pad1.05x0.95mm_HandSolder
R3: 10k; R_0603_1608Metric_Pad1.05x0.95mm_HandSolder
U1: L4931ABD33-TR; SOIC-8_3.9x4.9mm_P1.27mm
U2: STM32F103RCTx; LQFP-64_10x10mm_P0.5mm
Y1: 8MHz; Crystal_HC49-U_Vertical

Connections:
+3V3: C4.1, J1.1, J13.1, J14.6, U1.1, U2.1, U2.13, U2.19, U2.32, U2.48, U2.64
+5V: C1.1, J2.1, J14.7, R2.1, U1.8
/LED_BLANK: J14.3, U2.42
/LED_DATA_CK: J14.4, U2.21
/LED_DATA_OUT: J14.5, U2.23
/LED_LATCH: J14.2, U2.41
/NRST: J1.2, U2.7
/OSC_IN: C2.1, U2.5, Y1.1
/OSC_OUT: R1.1, U2.6
/SWDCLK: J1.3, U2.49
/SWDIO: J1.4, U2.46
/USB_DM: J2.2, U2.44
/USB_DP: J2.3, R2.2, U2.45
/col17: J3.1, U2.9
/col18: J4.1, U2.10
/col19: J5.1, U2.11
/col20: J6.1, U2.24
/row0: J7.1, U2.14
/row1: J8.1, U2.15
/row2: J9.1, U2.16
/row3: J10.1, U2.17
/row4: J11.1, U2.20
/row5: J12.1, U2.22
GND: C1.2, C2.2, C3.2, C4.2, J1.5, J2.5, J2.6, J13.3, J14.1, U1.2, U1.3, U1.6, U1.7, U2.12, U2.18, U2.31, U2.47, U2.63
unnamed: C3.1, R1.2, Y1.2
unnamed: J13.2, R3.2
unnamed: R3.1, U2.60

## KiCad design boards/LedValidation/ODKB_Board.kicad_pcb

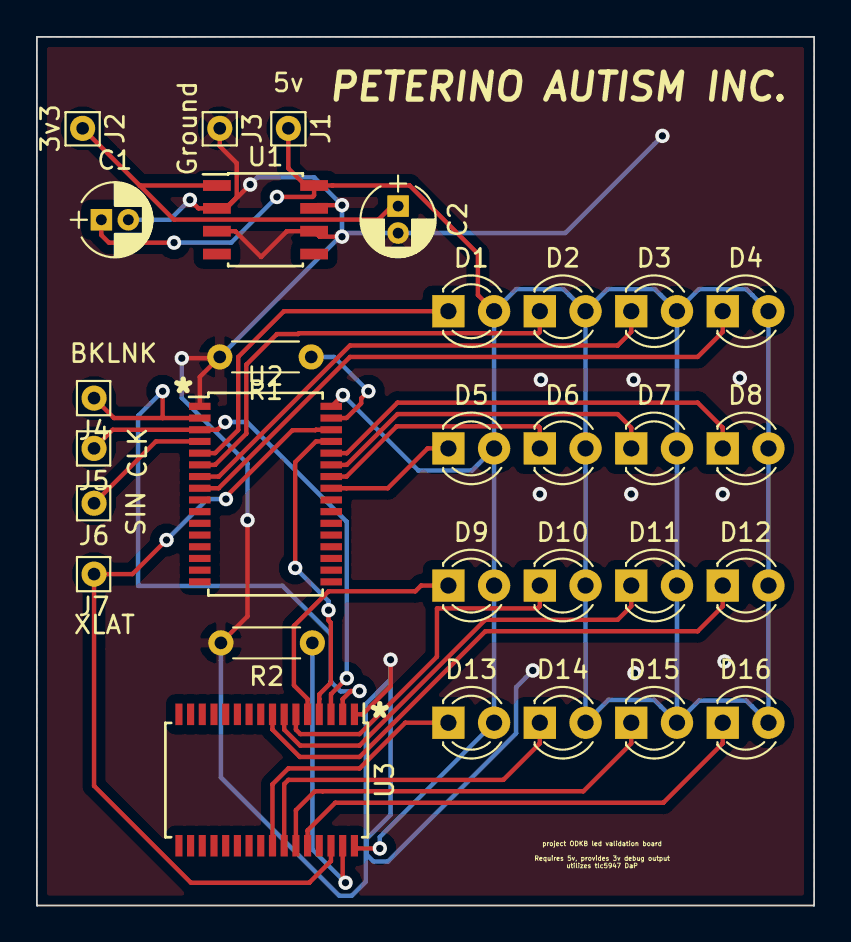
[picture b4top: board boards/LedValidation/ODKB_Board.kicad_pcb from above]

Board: 2 copper layers, 43.2 x 48.3 mm, 30 parts (0 on the bottom side), 26 nets.

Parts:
C1: 0.1uF; CP_Radial_D4.0mm_P1.50mm
C2: 2.2uF; CP_Radial_D4.0mm_P1.50mm
D1, D2, D3, D4, D5, D6, D7, D8, D9, D10, D11, D12, D13, D14, D15, D16: LED; LED_D3.0mm_FlatTop
J1: 5v; Pin_d0.7mm_L6.5mm_W1.8mm_FlatFork
J2: 3v3; Pin_d0.7mm_L6.5mm_W1.8mm_FlatFork
J3: Ground; Pin_d0.7mm_L6.5mm_W1.8mm_FlatFork
J4: BKLNK; Pin_d0.7mm_L6.5mm_W1.8mm_FlatFork
J5: CLK; Pin_d0.7mm_L6.5mm_W1.8mm_FlatFork
J6: SIN; Pin_d0.7mm_L6.5mm_W1.8mm_FlatFork
J7: XLAT; Pin_d0.7mm_L6.5mm_W1.8mm_FlatFork
R1, R2: 9.8k; R_Axial_DIN0204_L3.6mm_D1.6mm_P5.08mm_Horizontal
U1: L4931ABD33-TR; SOIC-8_3.9x4.9mm_Pitch1.27mm
U2, U3: TLC5947_DAP; TSSOP-32_6.1x11mm_Pitch0.65mm

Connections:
+3V3: C2.1, J2.1, U1.1
+5V: C1.1, D1.2, D2.2, D3.2, D4.2, D5.2, D6.2, D7.2, D8.2, D9.2, D10.2, D11.2, D12.2, D13.2, D14.2, D15.2, D16.2, J1.1, U1.8, U2.32, U3.32
/BLANK: J4.1, U2.2, U3.2
/CLK: J5.1, U2.3, U3.3
/SIN: J6.1, U2.4
/XLAT: J7.1, U2.30, U3.30
/led1: D1.1, U2.5
/led2: D2.1, U2.6
/led3: D3.1, U2.7
/led4: D4.1, U2.8
/led5: D5.1, U2.25
/led6: D6.1, U2.26
/led7: D7.1, U2.27
/led8: D8.1, U2.28
/led9: D9.1, U3.5
/led10: D10.1, U3.6
/led11: D11.1, U3.7
/led12: D12.1, U3.8
/led13: D13.1, U3.25
/led14: D14.1, U3.26
/led15: D15.1, U3.27
/led16: D16.1, U3.28
GND: C1.2, C2.2, J3.1, R1.2, R2.2, U1.2, U1.3, U1.6, U1.7, U2.1, U3.1
unnamed: R1.1, U2.31
unnamed: R2.1, U3.31
unnamed: U2.29, U3.4

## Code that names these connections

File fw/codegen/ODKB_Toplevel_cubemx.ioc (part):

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Mcu.Name=STM32F103R(C-D-E)Tx
Mcu.Package=LQFP64
Mcu.UserName=STM32F103RCTx
PA11.Mode=Device
PA11.Signal=USB_DM
PA12.Mode=Device
PA12.Signal=USB_DP
PB13.Mode=Simplex_Bidirectional_Master
PB13.Signal=SPI2_SCK
PB15.Mode=Simplex_Bidirectional_Master
PB15.Signal=SPI2_MOSI
PD0-OSC_IN.Mode=HSE-External-Oscillator
PD0-OSC_IN.Signal=RCC_OSC_IN
PD1-OSC_OUT.Mode=HSE-External-Oscillator
PD1-OSC_OUT.Signal=RCC_OSC_OUT
RCC.SYSCLKFreq_VALUE=48000000
RCC.SYSCLKSource=RCC_SYSCLKSOURCE_PLLCLK

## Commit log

2019-04-07 moved project to git
2019-07-23 gitignore
2019-07-23 flatted small project file structures
2019-07-23 Re-arranged project into hobby-boy mode
2019-07-23 renamed gay folder
2020-01-12 changed a lot of folders and started shatterwing
2020-01-13 restarted shatterwing thing
2020-01-13 MOAR RESEARCH BITHC
2020-10-05 its all done
